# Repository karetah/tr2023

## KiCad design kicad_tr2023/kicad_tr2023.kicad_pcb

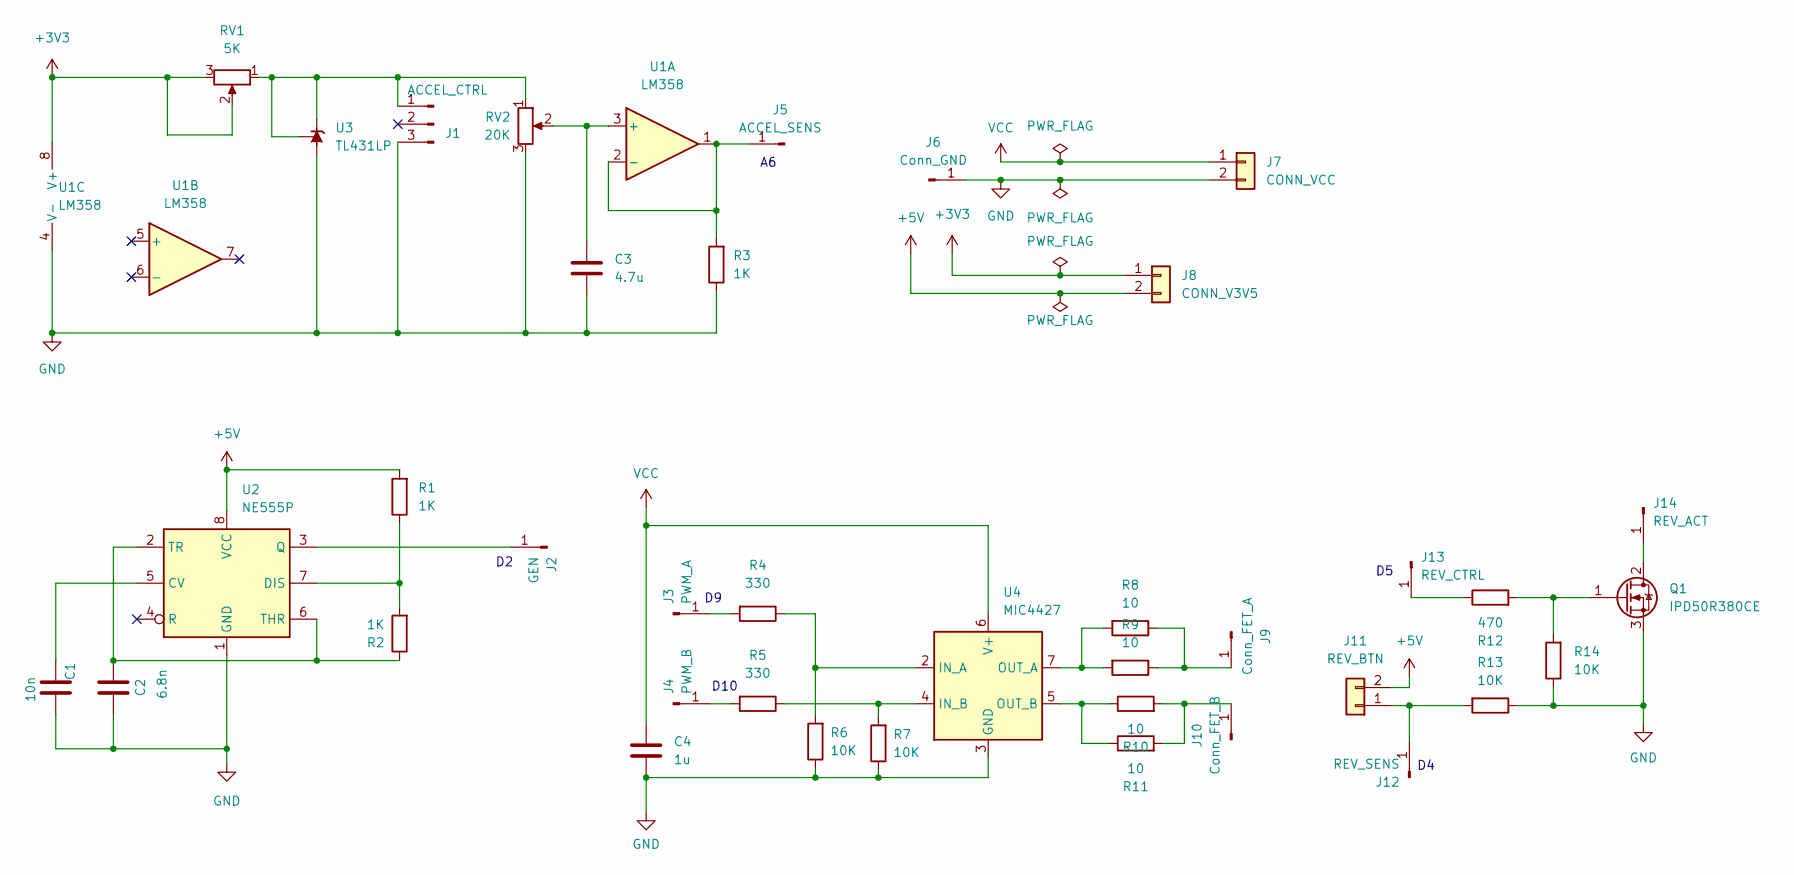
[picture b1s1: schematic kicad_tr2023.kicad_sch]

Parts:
C1: 10n; C_Disc_D3.0mm_W2.0mm_P2.50mm
C2: 6.8n; C_Disc_D3.0mm_W2.0mm_P2.50mm
C3: 4.7u; C_Disc_D7.0mm_W2.5mm_P5.00mm
C4: 1u; C_Disc_D3.0mm_W2.0mm_P2.50mm
J1: ACCEL_CTRL; FanPinHeader_1x03_P2.54mm_Vertical
J2: GEN; PinHeader_1x01_P2.54mm_Vertical
J3: PWM_A; PinHeader_1x01_P2.54mm_Vertical
J4: PWM_B; PinHeader_1x01_P2.54mm_Vertical
J5: ACCEL_SENS; PinHeader_1x01_P2.54mm_Vertical
J6: Conn_GND; PinHeader_1x01_P2.54mm_Vertical
J7: CONN_VCC; JST_PH_B2B-PH-K_1x02_P2.00mm_Vertical
J8: CONN_V3V5; JST_PH_B2B-PH-K_1x02_P2.00mm_Vertical
J9: Conn_FET_A; PinHeader_1x01_P2.54mm_Vertical
J10: Conn_FET_B; PinHeader_1x01_P2.54mm_Vertical
J11: REV_BTN; JST_PH_B2B-PH-K_1x02_P2.00mm_Vertical
J12: REV_SENS; PinHeader_1x01_P2.54mm_Vertical
J13: REV_CTRL; PinHeader_1x01_P2.54mm_Vertical
J14: REV_ACT; PinHeader_1x01_P2.54mm_Vertical
Q1: IPD50R380CE; TO-252-2
R1, R2, R3: 1K; R_Axial_DIN0207_L6.3mm_D2.5mm_P10.16mm_Horizontal
R4, R5: 330; R_Axial_DIN0207_L6.3mm_D2.5mm_P10.16mm_Horizontal
R6, R7, R13, R14: 10K; R_Axial_DIN0207_L6.3mm_D2.5mm_P10.16mm_Horizontal
R8, R9, R10, R11: 10; R_Axial_DIN0207_L6.3mm_D2.5mm_P10.16mm_Horizontal
R12: 470; R_Axial_DIN0207_L6.3mm_D2.5mm_P10.16mm_Horizontal
RV1: 5K; Potentiometer_ACP_CA9-V10_Vertical
RV2: 20K; Potentiometer_ACP_CA9-V10_Vertical
U1: LM358; DIP-8_W7.62mm
U2: NE555P; DIP-8_W7.62mm
U3: TL431LP; TO-92L_Wide
U4: MIC4427; DIP-8_W7.62mm

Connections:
+3V3: J8.1, RV1.2, RV1.3, U1.8 (V+)
+5V: J8.2, J11.2, R1.2, U2.8 (VCC)
GND: C1.1, C2.1, C3.2, C4.2, J1.3, J6.1, J7.2, Q1.3 (S), R3.1, R6.1, R7.1, R13.1, R14.1, RV2.3, U1.4 (V-), U2.1 (GND), U3.2 (A), U4.3 (GND)
unnamed: C1.2, U2.5 (CV)
unnamed: C2.2, R2.1, U2.2 (TR), U2.6 (THR)
unnamed: C3.1, RV2.2, U1.3 (+)
unnamed: J1.1, RV1.1, RV2.1, U3.1 (REF), U3.3 (K)
unnamed: J2.1, U2.3 (Q)
unnamed: J3.1, R4.2
unnamed: J4.1, R5.2
unnamed: J5.1, R3.2, U1.1, U1.2 (-)
unnamed: J9.1, R8.1, R9.1
unnamed: J10.1, R10.2, R11.2
unnamed: J11.1, J12.1, R13.2
unnamed: J13.1, R12.1
unnamed: J14.1, Q1.2 (D)
unnamed: Q1.1 (G), R12.2, R14.2
unnamed: R1.1, R2.2, U2.7 (DIS)
unnamed: R4.1, R6.2, U4.2 (IN_A)
unnamed: R5.1, R7.2, U4.4 (IN_B)
unnamed: R8.2, R9.2, U4.7 (OUT_A)
unnamed: R10.1, R11.1, U4.5 (OUT_B)
VCC: C4.1, J7.1, U4.6 (V+)

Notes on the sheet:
D10

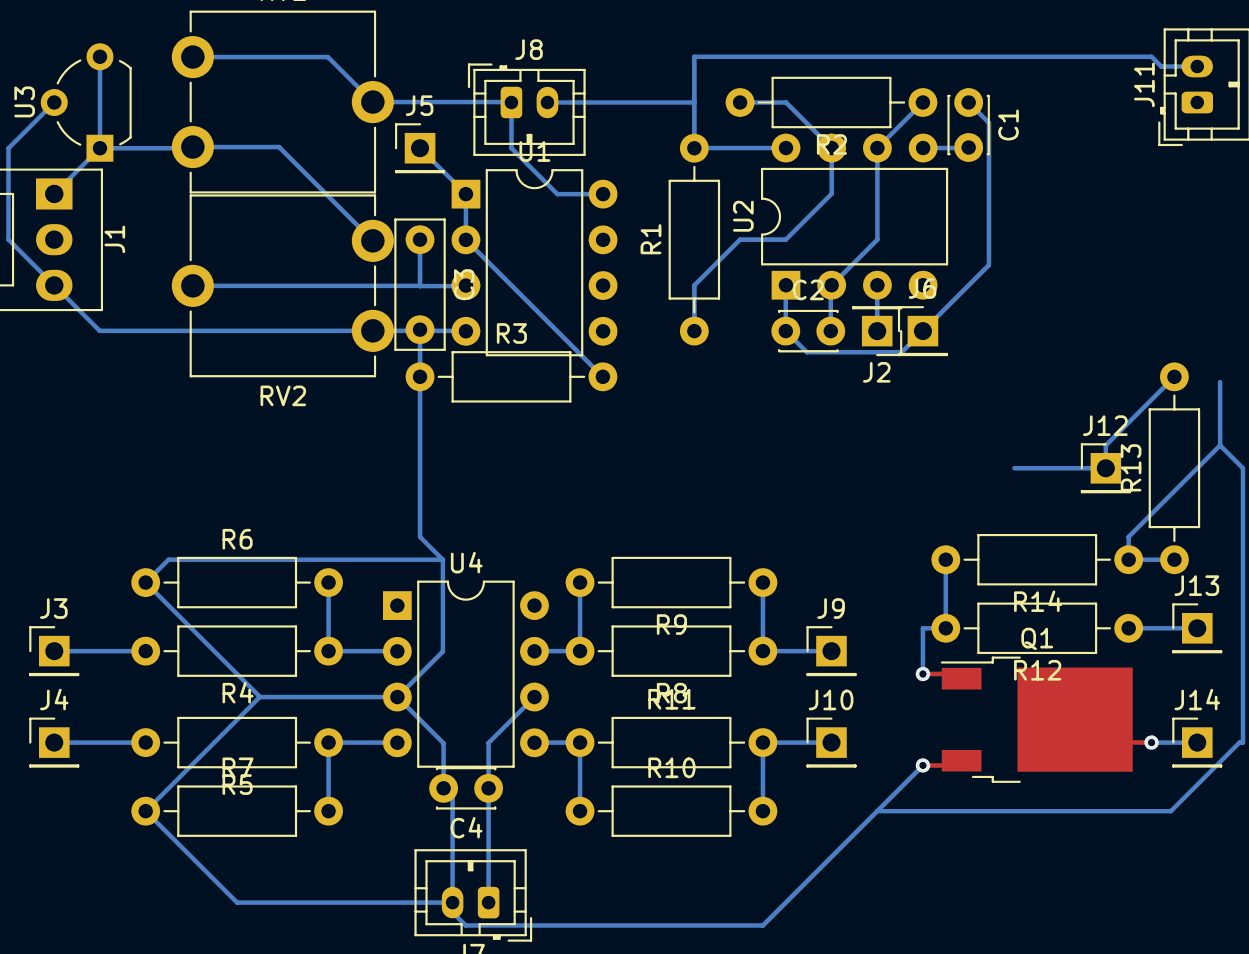
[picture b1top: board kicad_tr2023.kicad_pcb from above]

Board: 2 copper layers, 39 parts (0 on the bottom side), 23 nets.

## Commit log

2023-01-06 from 2022
2023-01-07 i've lost my PD1 :(
2023-06-22 add kicad blocks
2023-06-30 sync chg
2023-10-02 202310
